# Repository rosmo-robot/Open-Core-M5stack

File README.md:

!!Untested!!

OpenCore boards for use in the M5Stack system

[Version 1](https://github.com/rosmo-robot/Open-Core-M5stack/blob/main/v1/readme.md) uses ESP32devC-v4 development board

[Version 2](https://github.com/rosmo-robot/Open-Core-M5stack/tree/main/2.2) uses on-board ESP32 chip

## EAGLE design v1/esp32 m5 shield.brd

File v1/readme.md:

# Open-Core-M5stack
Adapter for ESP32-Dev-C &amp; M5stack modules. It can be viewed [on Altium](https://365.altium.com/files/CDB3C9AB-1C0E-4B25-A3A4-1780F1BBCA1A) or [Easy Eda](https://easyeda.com/editor#id=49352f7d047e4be9b435180f0d233d80)

It is used as a replacement for the 'core' modules in the M5stack system. It should be compatible with any [ESP32-DevKitC V4](https://www.aliexpress.com/item/1005001838731651.html)

When used with [Olimex ESP32 lipo](https://www.olimex.com/Products/IoT/ESP32/ESP32-DevKit-LiPo/open-source-hardware) it can provide an completely open hardware module in the  [M5 stack system](https://shop.m5stack.com/collections/stack-series). 

Includes a [UEXT socket](https://en.wikipedia.org/wiki/UEXT#Electrical_characteristics) for interfacing with [additional modules](https://www.olimex.com/Products/Modules/UEXT/) The UEXT pins can alternatively be used as breakout pins for jumper cables.

There are [other open hardware M5stack boards](https://oshwlab.com/Rosmo/m5-proto)

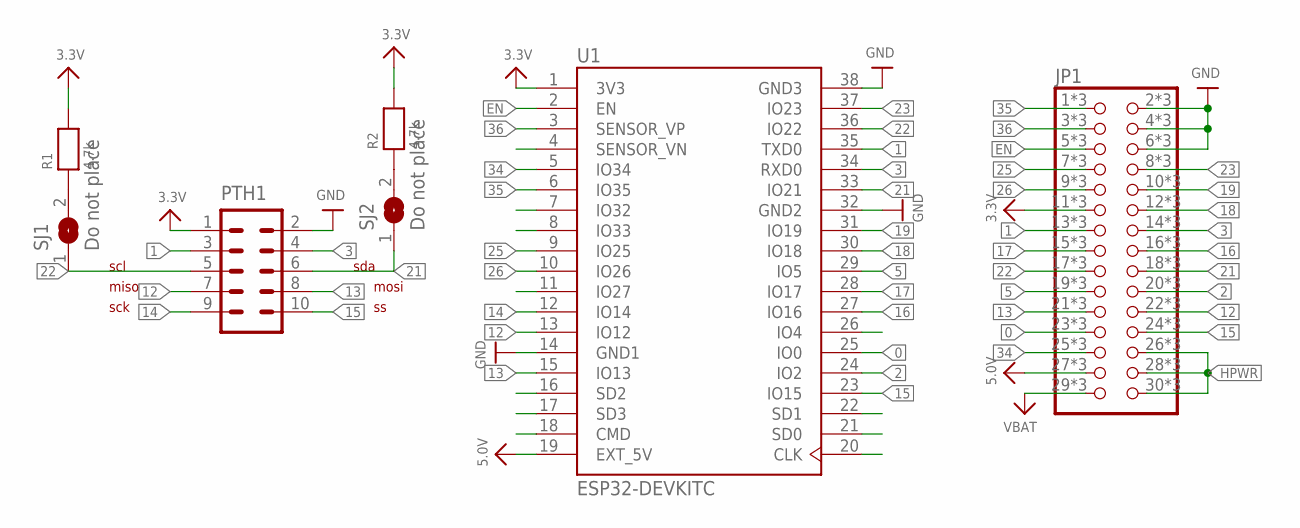
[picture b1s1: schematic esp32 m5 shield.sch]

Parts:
JP1: PINHD-2X15; 2X15
PTH1: ML10PTH; ML10-MALE
R1, R2: 4.7k; 0603-MINI
SJ1, SJ2: Do not place; SOLDERJUMPER_CLOSEDWIRE
U1: ESP32-DEVKITC; MODULE_ESP32-DEVKITC

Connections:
0: JP1.23, JP1.P$23 (23), JP1.P$53 (23), U1.25 (IO0)
1: JP1.13, JP1.P$13 (13), JP1.P$43 (13), PTH1.3, U1.35 (TXD0)
2: JP1.20, JP1.P$20 (20), JP1.P$50 (20), U1.24 (IO2)
3: JP1.14, JP1.P$14 (14), JP1.P$44 (14), PTH1.4, U1.34 (RXD0)
3.3V: JP1.11, JP1.P$11 (11), JP1.P$41 (11), PTH1.1, R1.2, R2.2, U1.1 (3V3)
5: JP1.19, JP1.P$19 (19), JP1.P$49 (19), U1.29 (IO5)
5.0V: JP1.27, JP1.P$27 (27), JP1.P$57 (27), U1.19 (EXT_5V)
12: JP1.22, JP1.P$22 (22), JP1.P$52 (22), PTH1.7, U1.13 (IO12)
13: JP1.21, JP1.P$21 (21), JP1.P$51 (21), PTH1.8, U1.15 (IO13)
14: PTH1.9, U1.12 (IO14)
15: JP1.24, JP1.P$24 (24), JP1.P$54 (24), PTH1.10, U1.23 (IO15)
16: JP1.16, JP1.P$16 (16), JP1.P$46 (16), U1.27 (IO16)
17: JP1.15, JP1.P$15 (15), JP1.P$45 (15), U1.28 (IO17)
18: JP1.12, JP1.P$12 (12), JP1.P$42 (12), U1.30 (IO18)
19: JP1.10, JP1.P$10 (10), JP1.P$40 (10), U1.31 (IO19)
21: JP1.18, JP1.P$18 (18), JP1.P$48 (18), PTH1.6, SJ2.1, U1.33 (IO21)
22: JP1.17, JP1.P$17 (17), JP1.P$47 (17), PTH1.5, SJ1.1, U1.36 (IO22)
23: JP1.8, JP1.P$8 (8), JP1.P$38 (8), U1.37 (IO23)
25: JP1.7, JP1.P$7 (7), JP1.P$37 (7), U1.9 (IO25)
26: JP1.9, JP1.P$9 (9), JP1.P$39 (9), U1.10 (IO26)
34: JP1.25, JP1.P$25 (25), JP1.P$55 (25), U1.5 (IO34)
35: JP1.1, JP1.P$1 (1), JP1.P$31 (1), U1.6 (IO35)
36: JP1.3, JP1.P$3 (3), JP1.P$33 (3), U1.3 (SENSOR_VP)
EN: JP1.5, JP1.P$5 (5), JP1.P$35 (5), U1.2 (EN)
GND: JP1.2, JP1.4, JP1.6, JP1.P$2 (2), JP1.P$4 (4), JP1.P$6 (6), JP1.P$32 (2), JP1.P$34 (4), JP1.P$36 (6), PTH1.2, U1.14 (GND1), U1.32 (GND2), U1.38 (GND3)
HPWR: JP1.26, JP1.28, JP1.30, JP1.P$26 (26), JP1.P$28 (28), JP1.P$30 (30), JP1.P$56 (26), JP1.P$58 (28), JP1.P$60 (30)
unnamed: R1.1, SJ1.2
unnamed: R2.1, SJ2.2
VBAT: JP1.29, JP1.P$29 (29), JP1.P$59 (29)

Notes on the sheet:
mosi
miso
sda
scl
sck

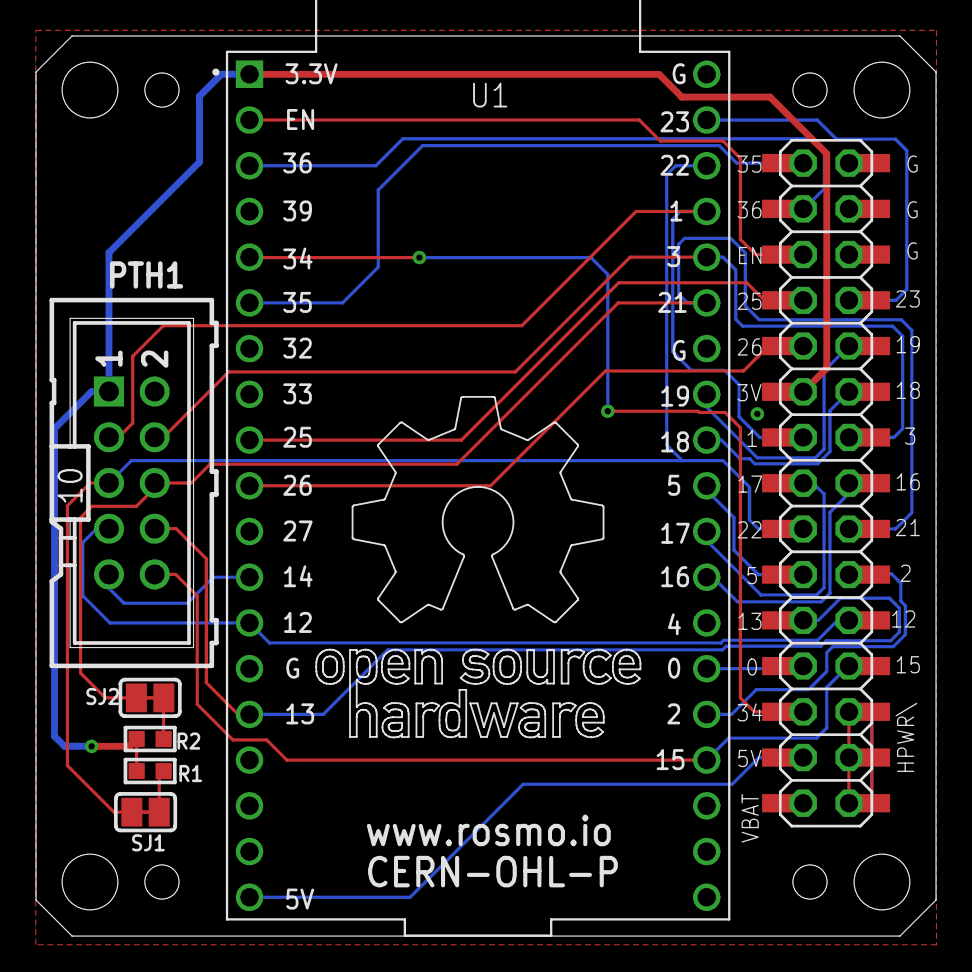
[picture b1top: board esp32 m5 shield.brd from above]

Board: 2 copper layers, 50.0 x 50.0 mm, 7 parts (0 on the bottom side), 29 nets.

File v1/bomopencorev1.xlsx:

Qty | Value | Device | Package | Parts | Description | Column1 | _1 | @ | Notes
1.0 | Do not place | ML10PTH | ML10-MALE | PTH1 | UEXT |  |  |  | https://octopart.com/search?currency=GBP&q=66506-001lf&specs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
2.0 | 4.7k | R-EU_0204/7 | 0204/7 | R1, R2 | RESISTOR, 1/4W
1.0 | 5330-M5CONN2X15F | PINHD-2X15 | 2X15 | JP1 | PIN HEADER |  |  |  | https://www.futurashop.it/connettore-per-m5stack-2x15pin-fem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
2.0 | Do not place | SOLDERJUMPERCLOSED | SOLDERJUMPER_CLOSEDWIRE | SJ1, SJ2 | SMD Solder JUMPER
2.0 | FEMALE HEADER | FEMALE HEADER | FEMALE HEADER 2.54 | JP2,JP3 | FEMALER HEADER

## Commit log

2022-01-04 Added first version for review
2022-01-04 Update README.md
    Added links to Olimex https://www.olimex.com/Products/Modules/
2022-01-04 Add files via upload
    Added picture
2022-01-04 Update README.md
    Added picture
2022-01-04 Update README.md
    Added easy eda link https://easyeda.com/editor#id=49352f7d047e4be9b435180f0d233d80
2022-01-04 Update README.md
    Added better link: https://365.altium.com/files/CDB3C9AB-1C0E-4B25-A3A4-1780F1BBCA1A
2022-01-09 Update README.md
    de-crappified a bit
2022-01-21 Version with through hole resistors
2022-01-21 Added links to parts
2022-01-27 Add files via upload
    Added v1 gerber
2022-01-27 v1.0 BOM
2022-01-27 Added v1 readme
2022-01-27 Added v1 & v2 links
2022-01-27 Added v1 files
2022-01-27 Added readme for v2
2022-01-27 Tidy, provisional BOM
2022-01-28 Organised a bit
2022-02-01 Added USB back in
2022-02-01 Added GPIO of various M5 shields
2022-02-01 Update schematic
2022-02-01 added gps
    https://shop.pimoroni.com/products/pa1010d-gps-breakout
2022-02-06 Added link to EasyEDA project
2022-02-06 Updated links, added images
2022-02-06 EasyEDA link
2022-02-06 Updated images with correct headers
2022-02-06 Better images
2022-02-06 Silkscreen changes
2022-02-23 Untested files for review
2022-02-23 Added Altium link
    https://365.altium.com/files/649C7BFA-BEAC-4A11-B612-F499FA4A752B
2022-02-23 added easyEDA
    https://easyeda.com/editor#id=b0c915455cd342b9a03f863e1992dc43|42f8b3c53ee042b4857c136aa38183c5
2022-02-23 Better image
2022-04-20 BOM files as ordered
2022-05-04 Create contributor
    Placeholder
2022-05-04 Update and rename contributor to contributor.md
    Added some stuff
2022-05-08 Reverse LCD pins
    The LCD pins were the wrong way around in v2.1. The files here simply reverse the orientation of the LCD.
2022-05-08 Gerber & EasyEDA files
2022-05-08 Same as v2.1
2022-05-08 Delete Gerber_NEW_PCB copy(LCD flip) copy.zip
    fixing silkscreen
2022-05-08 Gerber with correct LCD pins & Silkscreen
2022-05-08 Add image
2022-05-24 link to screen
    https://www.aliexpress.com/item/32859772356.html
2022-05-25 Seed studio format with links
2022-05-31 featherwing version

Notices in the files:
v1/esp32 m5 shield.brd:
CERN-OHL-P
parts and their libraries:
microbuilder: This work is placed in the public domain, and may be freely used for commercial and non-commercial work with the following conditions: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
